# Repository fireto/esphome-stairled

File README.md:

# esphome-stairled

esphome-stairled based on ESP Home with HomeAssistant integration via MQTT or native esphome API

It controls 16 PWM outputs via PCA9685 i2c LED controller
[datasheet](https://www.nxp.com/docs/en/data-sheet/PCA9685.pdf)

Optional Temperature and barometric pressure sensor: 
[BMP180](https://www.digikey.com/htmldatasheets/production/856385/0/0/1/BMP180-Datasheet.pdf)

in order to compile and deploy this project you need to get [esphome.io](https://esphome.io)

```podman run --rm -v "${PWD}":/config --device=/dev/ttyUSB0 -it esphome/esphome:latest run ./stairLed.yml```

BOM

* [1x Olimex ESP32POE](https://www.olimex.com/Products/IoT/ESP32/ESP32-POE/open-source-hardware)
* [1x Olimex UEXT CABLE-IDC10-15cm](https://www.olimex.com/Products/Modules/Adapters/CABLE-IDC10-15cm/)
* [1x PCA9685PW 16 Channel 12-bit PWM/Servo Driver-I2C interface](https://www.aliexpress.com/item/1005005973866782.html)
* [1x DC/DC BUCK 3A MP1584 adjustable buck module regulator LM2596S](https://www.aliexpress.com/item/32841466894.html)
* [1x BMP180 Digital Barometric Pressure Sensor](https://www.aliexpress.com/item/32709141948.html)
* [2x RJ45 PCB connector](https://vikiwat.com/product/19790/konektor-rj45-f-pcb.html)
* [5x4, 1x6, Female pin headers ]
* [2x10 Male pin headers]
* [Plastic DIN mounted box-P912036](https://eshop-bg.com/produkt/%d0%bf%d0%bb%d0%b0%d1%81%d1%82%d0%bc%d0%b0%d1%81%d0%be%d0%b2%d0%b0-%d0%ba%d1%83%d1%82%d0%b8%d1%8f-%d0%b7%d0%b0-din-%d1%88%d0%b8%d0%bd%d0%b0-85x58x157%d0%bc%d0%bc/)
* [2x Panasonic PIR sensor](https://www.farnell.com/datasheets/2267095.pdf)

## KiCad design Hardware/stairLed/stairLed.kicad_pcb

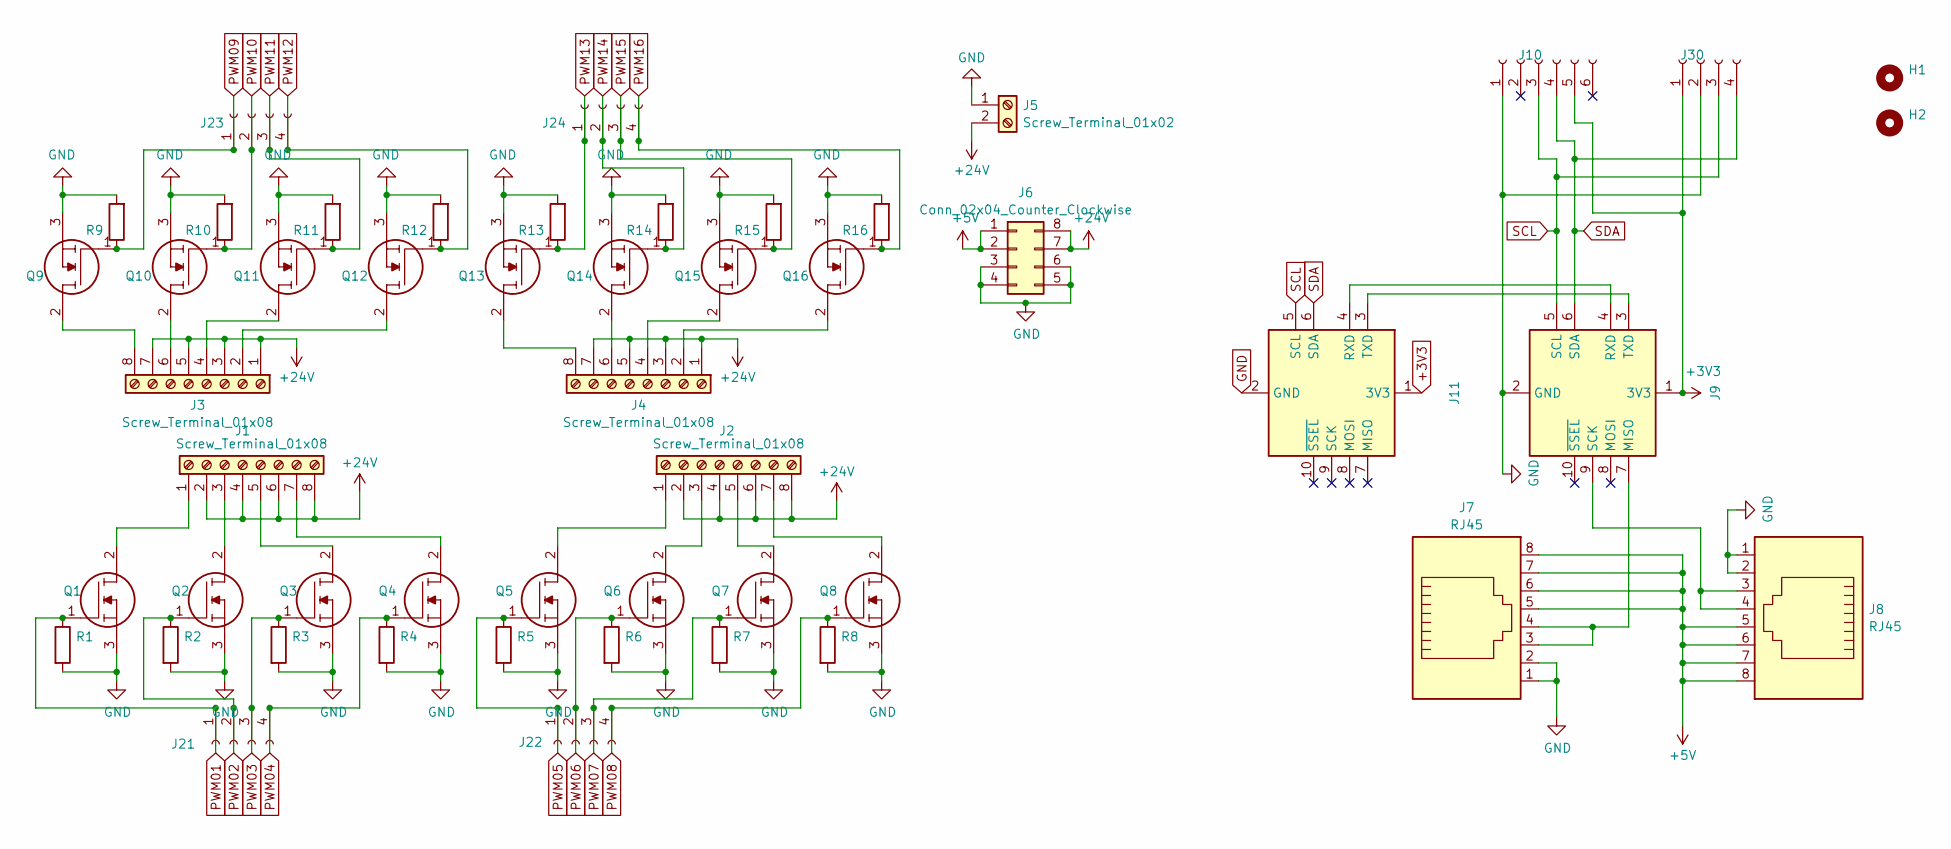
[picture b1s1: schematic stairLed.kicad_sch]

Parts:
H1, H2: MountingHole_3.2mm_M3
J1, J2, J3, J4: Screw_Terminal_01x08; TerminalBlock_bornier-8_P5.08mm
J5: Screw_Terminal_01x02; TerminalBlock_bornier-2_P5.08mm
J6: Conn_02x04_Counter_Clockwise; MP1584EN_dc-dc_module
J7, J8: RJ45; RJ45-vikvat-30757
J9, J11: PinSocket_2x05_P2.54mm_Vertical
J10: PinSocket_1x06_P2.54mm_Vertical
J21, J22, J23, J24, J30: PinSocket_1x04_P2.54mm_Vertical
Q1, Q2, Q3, Q4, Q5, Q6, Q7, Q8, Q9, Q10, Q11, Q12, Q13, Q14, Q15, Q16: FDD8447L; Manufacturer_Part_Number FDD8447L; Mouser Part Number 512-FDD8447L
R1, R2, R3, R4, R5, R6, R7, R8, R9, R10, R11, R12, R13, R14, R15, R16: R_0805_2012Metric

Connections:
+3V3: J9.1 (3V3), J10.5, J11.1 (3V3), J30.1
+5V: J6.1, J6.2, J7.5, J7.6, J7.7, J7.8, J8.5, J8.6, J8.7, J8.8
+24V: J1.2, J1.4, J1.6, J1.8, J2.2, J2.4, J2.6, J2.8, J3.1, J3.3, J3.5, J3.7, J4.1, J4.3, J4.5, J4.7, J5.2, J6.7, J6.8
GND: J5.1, J6.3, J6.4, J6.5, J6.6, J7.1, J7.2, J8.1, J8.2, J9.2 (GND), J10.1, J11.2 (GND), J30.2, Q1.3, Q2.3, Q3.3, Q4.3, Q5.3, Q6.3, Q7.3, Q8.3, Q9.3, Q10.3, Q11.3, Q12.3, Q13.3, Q14.3, Q15.3, Q16.3, R1.2, R2.2, R3.2, R4.2, R5.2, R6.2, R7.2, R8.2, R9.2, R10.2, R11.2, R12.2, R13.2, R14.2, R15.2, R16.2
unnamed: J1.1, Q1.2
unnamed: J1.3, Q2.2
unnamed: J1.5, Q3.2
unnamed: J1.7, Q4.2
unnamed: J2.1, Q5.2
unnamed: J2.3, Q6.2
unnamed: J2.5, Q7.2
unnamed: J2.7, Q8.2
unnamed: J3.2, Q12.2
unnamed: J3.4, Q11.2
unnamed: J3.6, Q10.2
unnamed: J3.8, Q9.2
unnamed: J4.2, Q16.2
unnamed: J4.4, Q15.2
unnamed: J4.6, Q14.2
unnamed: J4.8, Q13.2
unnamed: J7.3, J7.4, J9.7 (MISO)
unnamed: J8.3, J8.4, J9.9 (SCK)
unnamed: J9.4 (RXD), J11.4 (RXD)
unnamed: J9.3 (TXD), J11.3 (TXD)
PWM01: J21.1, Q1.1, R1.1
PWM02: J21.2, Q2.1, R2.1
PWM03: J21.3, Q3.1, R3.1
PWM04: J21.4, Q4.1, R4.1
PWM05: J22.1, Q5.1, R5.1
PWM06: J22.2, Q6.1, R6.1
PWM07: J22.3, Q7.1, R7.1
PWM08: J22.4, Q8.1, R8.1
PWM09: J23.1, Q9.1, R9.1
PWM10: J23.2, Q10.1, R10.1
PWM11: J23.3, Q11.1, R11.1
PWM12: J23.4, Q12.1, R12.1
PWM13: J24.1, Q13.1, R13.1
PWM14: J24.2, Q14.1, R14.1
PWM15: J24.3, Q15.1, R15.1
PWM16: J24.4, Q16.1, R16.1
SCL: J9.5 (SCL), J10.3, J11.5 (SCL), J30.3
SDA: J9.6 (SDA), J10.4, J11.6 (SDA), J30.4

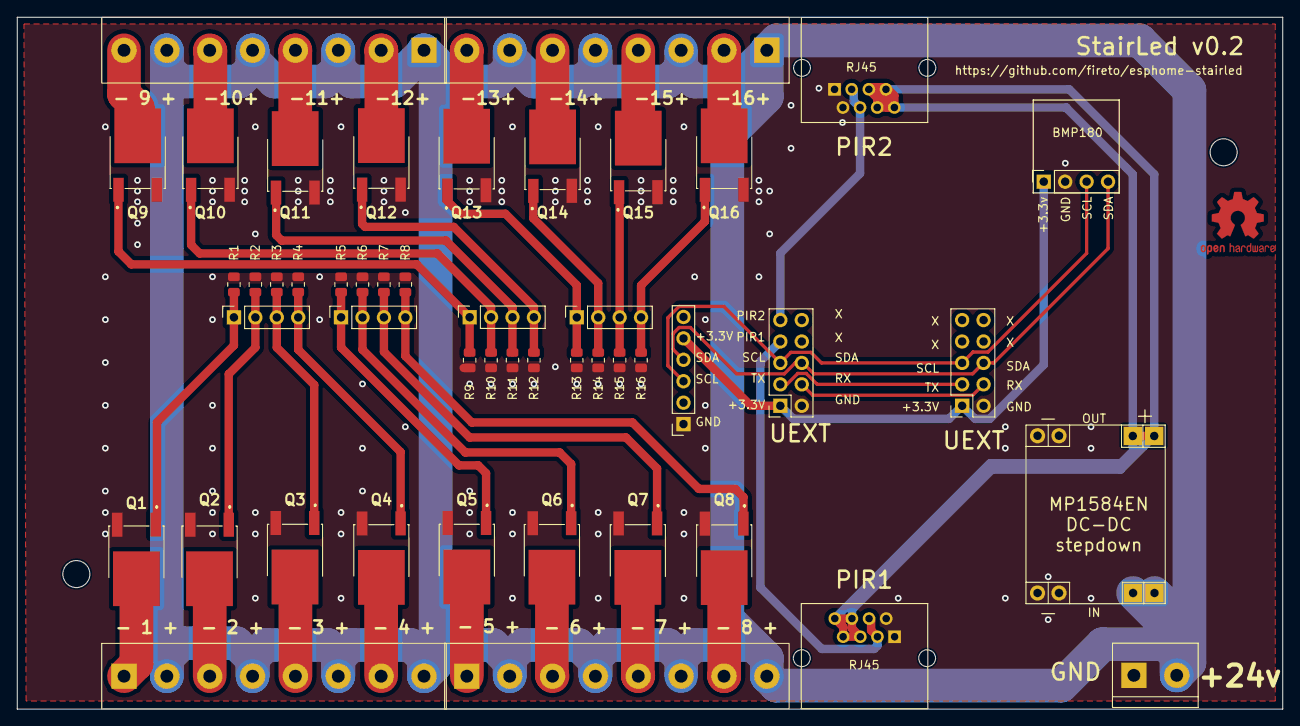
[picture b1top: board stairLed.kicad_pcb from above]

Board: 2 copper layers, 150.0 x 82.0 mm, 50 parts (0 on the bottom side), 42 nets.

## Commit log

2024-09-03 adding KiCad hardware files
2024-09-03 fixing common configuration, renaming main yaml file
2025-03-07 update .gitignore and README for improved documentation and ignore patterns; fix YAML configuration for ESP32
2025-04-11 switch webserver to v3
2025-04-11 added effects, added combined script for OnOff, halloween mode
2025-08-11 migrate to state machine
2026-04-24 add loglevel selector and set log level on_boot
2026-04-24 configure ethernet with new esphome syntax and add ignore_strapping_warning false for GPIO12
2026-04-24 fix bugs and refactor stair LED scripts
    - fix chip revision warning (minimum_chip_revision: 3.0)
    - fix nightTransLength substitution replacing incorrect transition_length values
    - fix double step16 turn-off in fadeOffBottomTop
    - fix missing delay after step16 in fadeOffTopBottom
    - fix fade-on/fade-off race in state machine on_leave (stop fadeOn before starting fadeOff)
    - nightMode: run fadeOffBottomTop to clear intermediate steps, then reset state machine via idleTimeout
2026-06-12 Exposed Internal EPS32 temperature
2026-06-15 Emit ascended/descended events to HA at end of climb animations
    Add a template 'event' entity (Staircase Motion) and fire 'ascended' at
    the end of fadeOnBottomTop and 'descended' at the end of fadeOnTopBottom.
    Lets HA act on 'reached the top/bottom' (e.g. light the arrival-floor
    ceiling light) without hardcoding HA entity ids in firmware.
2026-06-15 Ceiling as step 17: delay on-event to last step max + emit off-events
    Delay the ascended/descended events by one ON transition so the ceiling
    lights fire only after the last LED step reaches max (not mid-fade). Add
    ascended_off/descended_off events at the end of each OFF animation so HA
    can fade the ceiling out as the final step instead of on a 5-min timer.
2026-06-16 Fix step 1-5 flicker, off/on fade race, and PIR delayed_off
    - pca9685: set phase_balancer to none so high-channel PWM pulses no
    longer wrap past the cycle reset; eliminates steps 1-5 flickering when
    other steps fade.
    - state_machine: run stopAll on entering occupiedBottom/occupiedTop so a
    still-draining off-fade can't run concurrently with the new on-fade.
    - binary_sensor: reduce both PIR delayed_off filters from 10s to 2s.
2026-06-16 gitignore: exclude editor .history/ snapshots
2026-06-16 Move device domain to secrets; drop identifying wifi comments
    - Replace hardcoded $domainName substitution with !secret domainName on
    both the ethernet and wifi domain options.
    - Remove commented-out alternate wifi SSIDs that named a location/person.
2026-06-16 Add Home Assistant Bluetooth proxy (BLE tracker + connectable proxy)
